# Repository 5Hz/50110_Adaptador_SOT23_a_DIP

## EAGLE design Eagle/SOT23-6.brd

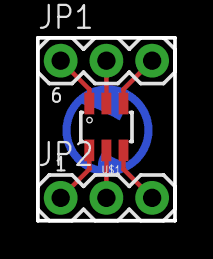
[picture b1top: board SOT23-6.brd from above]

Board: 2 copper layers, 7.6 x 10.2 mm, 4 parts (1 on the bottom side), 6 nets.

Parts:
JP1, JP2: 1X03
LOGO1: LOGO_5HZ_CIRC_COOPER_5MM; 5HZ_LOGO_CIRC_COOPER_5MM
U$1: XN04312SOT; SOT23-6

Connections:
unnamed: JP1.3, U$1.3
unnamed: JP1.2, U$1.2
unnamed: JP1.1, U$1.1
unnamed: JP2.2, U$1.5
unnamed: JP2.1, U$1.6
unnamed: JP2.3, U$1.4

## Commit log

2014-01-14 creación
